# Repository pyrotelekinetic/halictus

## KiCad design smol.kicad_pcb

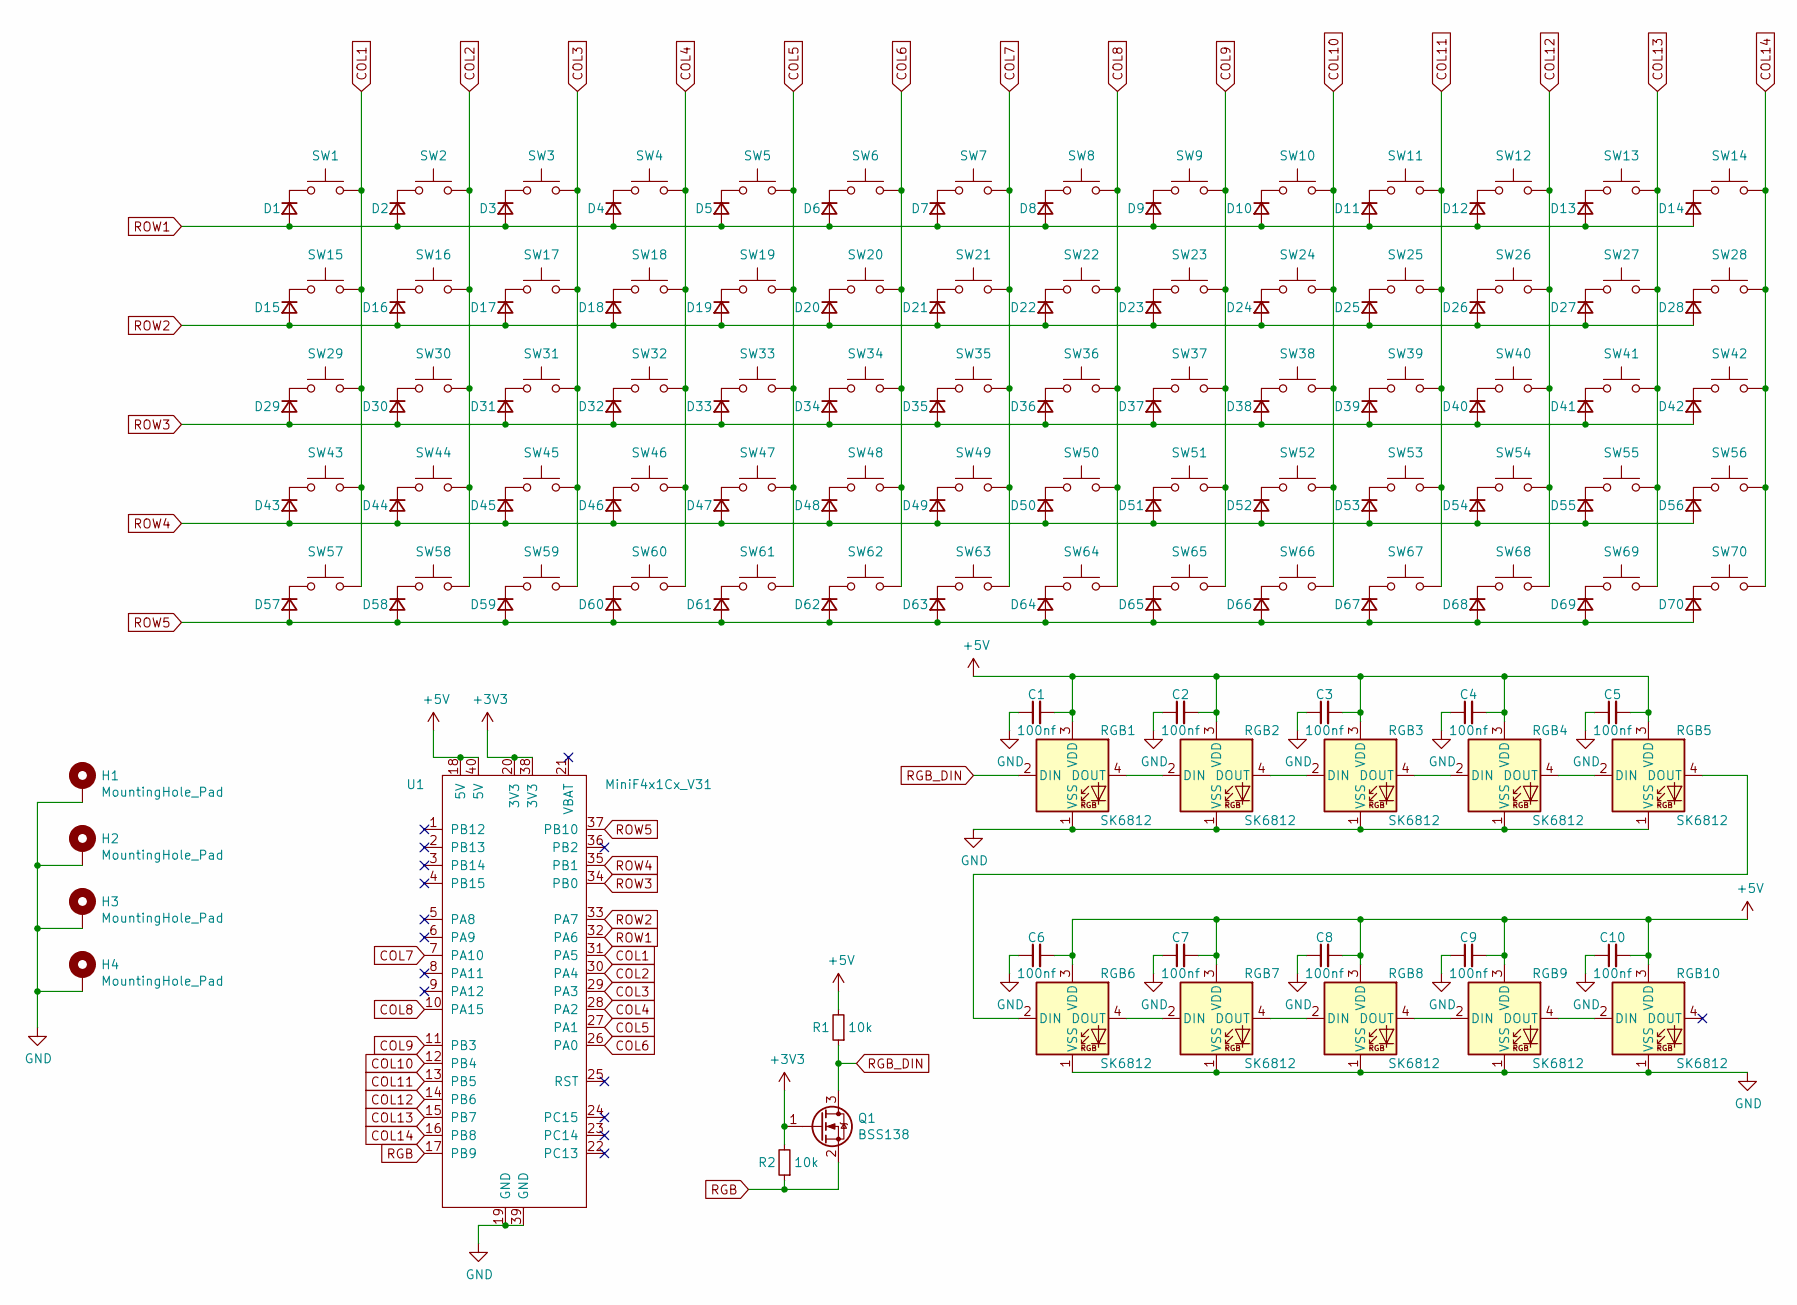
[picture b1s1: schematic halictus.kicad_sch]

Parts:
C1, C2, C3, C4, C5, C6, C7, C8, C9, C10: 100nf; C_0603_1608Metric_Pad1.08x0.95mm_HandSolder
D1, D2, D3, D4, D5, D6, D7, D8, D9, D10, D11, D12, D13, D14, D15, D16, D17, D18, D19, D20, D21, D22, D23, D24, D25, D26, D27, D28, D29, D30, D31, D32, D33, D34, D35, D36, D37, D38, D39, D40, D41, D42, D43, D44, D45, D46, D47, D48, D49, D50, D51, D52, D53, D54, D55, D56, D57, D58, D59, D60, D61, D62, D63, D64, D65, D66, D67, D68, D69, D70: D_Small; D_SOD-123
H1, H2, H3, H4: MountingHole_Pad; MountingHole_2.2mm_M2_Pad_TopBottom
Q1: BSS138; SOT-23
R1, R2: 10k; R_0603_1608Metric_Pad0.98x0.95mm_HandSolder
RGB1, RGB2, RGB3, RGB4, RGB5, RGB6, RGB7, RGB8, RGB9, RGB10: SK6812; LED_SK6812_PLCC4_5.0x5.0mm_P3.2mm
SW1, SW2, SW3, SW4, SW5, SW6, SW7, SW8, SW9, SW10, SW11, SW12, SW13, SW16, SW17, SW18, SW19, SW20, SW21, SW22, SW23, SW24, SW25, SW26, SW27, SW28, SW29, SW30, SW31, SW32, SW33, SW34, SW35, SW36, SW37, SW38, SW39, SW40, SW41, SW44, SW45, SW46, SW47, SW48, SW49, SW50, SW51, SW52, SW53, SW54, SW55, SW56, SW57, SW58, SW59, SW60, SW61, SW62, SW64, SW65, SW66, SW67, SW68, SW69, SW70: 1U; MXOnly-1U-NoLED
SW14, SW15, SW42, SW43: 2U; MXOnly-2U-NoLED
SW63: 2U; MXOnly-2U-ReversedStabilizers-NoLED
U1: MiniF4x1Cx_V31

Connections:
+3V3: Q1.1 (G), R2.2, U1.20 (3V3), U1.38 (3V3)
+5V: C1.2, C2.2, C3.2, C4.2, C5.2, C6.2, C7.2, C8.2, C9.2, C10.2, R1.2, RGB1.3 (VDD), RGB2.3 (VDD), RGB3.3 (VDD), RGB4.3 (VDD), RGB5.3 (VDD), RGB6.3 (VDD), RGB7.3 (VDD), RGB8.3 (VDD), RGB9.3 (VDD), RGB10.3 (VDD), U1.18 (5V), U1.40 (5V)
COL1: SW1.2, SW15.2, SW29.2, SW43.2, SW57.2, U1.31 (PA5)
COL2: SW2.2, SW16.2, SW30.2, SW44.2, SW58.2, U1.30 (PA4)
COL3: SW3.2, SW17.2, SW31.2, SW45.2, SW59.2, U1.29 (PA3)
COL4: SW4.2, SW18.2, SW32.2, SW46.2, SW60.2, U1.28 (PA2)
COL5: SW5.2, SW19.2, SW33.2, SW47.2, SW61.2, U1.27 (PA1)
COL6: SW6.2, SW20.2, SW34.2, SW48.2, SW62.2, U1.26 (PA0)
COL7: SW7.2, SW21.2, SW35.2, SW49.2, SW63.2, U1.7 (PA10)
COL8: SW8.2, SW22.2, SW36.2, SW50.2, SW64.2, U1.10 (PA15)
COL9: SW9.2, SW23.2, SW37.2, SW51.2, SW65.2, U1.11 (PB3)
COL10: SW10.2, SW24.2, SW38.2, SW52.2, SW66.2, U1.12 (PB4)
COL11: SW11.2, SW25.2, SW39.2, SW53.2, SW67.2, U1.13 (PB5)
COL12: SW12.2, SW26.2, SW40.2, SW54.2, SW68.2, U1.14 (PB6)
COL13: SW13.2, SW27.2, SW41.2, SW55.2, SW69.2, U1.15 (PB7)
COL14: SW14.2, SW28.2, SW42.2, SW56.2, SW70.2, U1.16 (PB8)
GND: C1.1, C2.1, C3.1, C4.1, C5.1, C6.1, C7.1, C8.1, C9.1, C10.1, H1.1, H2.1, H3.1, H4.1, RGB1.1 (VSS), RGB2.1 (VSS), RGB3.1 (VSS), RGB4.1 (VSS), RGB5.1 (VSS), RGB6.1 (VSS), RGB7.1 (VSS), RGB8.1 (VSS), RGB9.1 (VSS), RGB10.1 (VSS), U1.19 (GND), U1.39 (GND)
unnamed: D1.1 (K), SW1.1
unnamed: D2.1 (K), SW2.1
unnamed: D3.1 (K), SW3.1
unnamed: D4.1 (K), SW4.1
unnamed: D5.1 (K), SW5.1
unnamed: D6.1 (K), SW6.1
unnamed: D7.1 (K), SW7.1
unnamed: D8.1 (K), SW8.1
unnamed: D9.1 (K), SW9.1
unnamed: D10.1 (K), SW10.1
unnamed: D11.1 (K), SW11.1
unnamed: D12.1 (K), SW12.1
unnamed: D13.1 (K), SW13.1
unnamed: D14.1 (K), SW14.1
unnamed: D15.1 (K), SW15.1
unnamed: D16.1 (K), SW16.1
unnamed: D17.1 (K), SW17.1
unnamed: D18.1 (K), SW18.1
unnamed: D19.1 (K), SW19.1
unnamed: D20.1 (K), SW20.1
unnamed: D21.1 (K), SW21.1
unnamed: D22.1 (K), SW22.1
unnamed: D23.1 (K), SW23.1
unnamed: D24.1 (K), SW24.1
unnamed: D25.1 (K), SW25.1
unnamed: D26.1 (K), SW26.1
unnamed: D27.1 (K), SW27.1
unnamed: D28.1 (K), SW28.1
unnamed: D29.1 (K), SW29.1
unnamed: D30.1 (K), SW30.1
unnamed: D31.1 (K), SW31.1
unnamed: D32.1 (K), SW32.1
unnamed: D33.1 (K), SW33.1
unnamed: D34.1 (K), SW34.1
unnamed: D35.1 (K), SW35.1
unnamed: D36.1 (K), SW36.1
unnamed: D37.1 (K), SW37.1
unnamed: D38.1 (K), SW38.1
unnamed: D39.1 (K), SW39.1
unnamed: D40.1 (K), SW40.1
unnamed: D41.1 (K), SW41.1
unnamed: D42.1 (K), SW42.1
unnamed: D43.1 (K), SW43.1
unnamed: D44.1 (K), SW44.1
unnamed: D45.1 (K), SW45.1
unnamed: D46.1 (K), SW46.1
unnamed: D47.1 (K), SW47.1
unnamed: D48.1 (K), SW48.1
unnamed: D49.1 (K), SW49.1
unnamed: D50.1 (K), SW50.1
unnamed: D51.1 (K), SW51.1
unnamed: D52.1 (K), SW52.1
unnamed: D53.1 (K), SW53.1
unnamed: D54.1 (K), SW54.1
unnamed: D55.1 (K), SW55.1
unnamed: D56.1 (K), SW56.1
unnamed: D57.1 (K), SW57.1
unnamed: D58.1 (K), SW58.1
unnamed: D59.1 (K), SW59.1
unnamed: D60.1 (K), SW60.1
unnamed: D61.1 (K), SW61.1
unnamed: D62.1 (K), SW62.1
unnamed: D63.1 (K), SW63.1
unnamed: D64.1 (K), SW64.1
unnamed: D65.1 (K), SW65.1
unnamed: D66.1 (K), SW66.1
unnamed: D67.1 (K), SW67.1
unnamed: D68.1 (K), SW68.1
unnamed: D69.1 (K), SW69.1
unnamed: D70.1 (K), SW70.1
unnamed: RGB1.4 (DOUT), RGB2.2 (DIN)
unnamed: RGB2.4 (DOUT), RGB3.2 (DIN)
unnamed: RGB3.4 (DOUT), RGB4.2 (DIN)
unnamed: RGB4.4 (DOUT), RGB5.2 (DIN)
unnamed: RGB5.4 (DOUT), RGB6.2 (DIN)
unnamed: RGB6.4 (DOUT), RGB7.2 (DIN)
unnamed: RGB7.4 (DOUT), RGB8.2 (DIN)
unnamed: RGB8.4 (DOUT), RGB9.2 (DIN)
unnamed: RGB9.4 (DOUT), RGB10.2 (DIN)
RGB: Q1.2 (S), R2.1, U1.17 (PB9)
RGB_DIN: Q1.3 (D), R1.1, RGB1.2 (DIN)
ROW1: D1.2 (A), D2.2 (A), D3.2 (A), D4.2 (A), D5.2 (A), D6.2 (A), D7.2 (A), D8.2 (A), D9.2 (A), D10.2 (A), D11.2 (A), D12.2 (A), D13.2 (A), D14.2 (A), U1.32 (PA6)
ROW2: D15.2 (A), D16.2 (A), D17.2 (A), D18.2 (A), D19.2 (A), D20.2 (A), D21.2 (A), D22.2 (A), D23.2 (A), D24.2 (A), D25.2 (A), D26.2 (A), D27.2 (A), D28.2 (A), U1.33 (PA7)
ROW3: D29.2 (A), D30.2 (A), D31.2 (A), D32.2 (A), D33.2 (A), D34.2 (A), D35.2 (A), D36.2 (A), D37.2 (A), D38.2 (A), D39.2 (A), D40.2 (A), D41.2 (A), D42.2 (A), U1.34 (PB0)
ROW4: D43.2 (A), D44.2 (A), D45.2 (A), D46.2 (A), D47.2 (A), D48.2 (A), D49.2 (A), D50.2 (A), D51.2 (A), D52.2 (A), D53.2 (A), D54.2 (A), D55.2 (A), D56.2 (A), U1.35 (PB1)
ROW5: D57.2 (A), D58.2 (A), D59.2 (A), D60.2 (A), D61.2 (A), D62.2 (A), D63.2 (A), D64.2 (A), D65.2 (A), D66.2 (A), D67.2 (A), D68.2 (A), D69.2 (A), D70.2 (A), U1.37 (PB10)

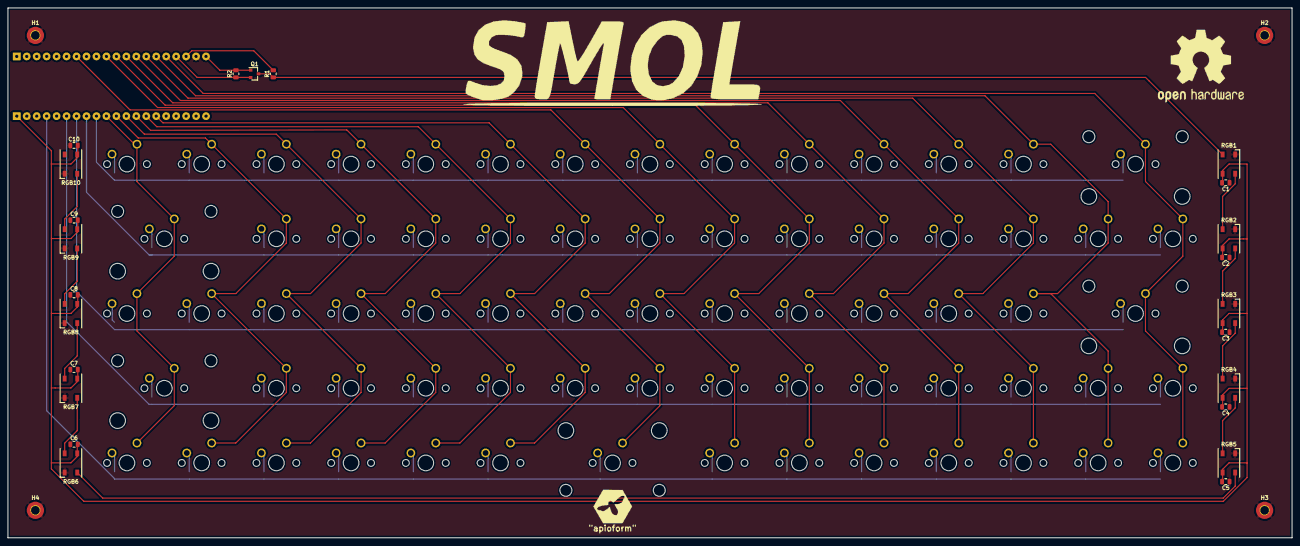
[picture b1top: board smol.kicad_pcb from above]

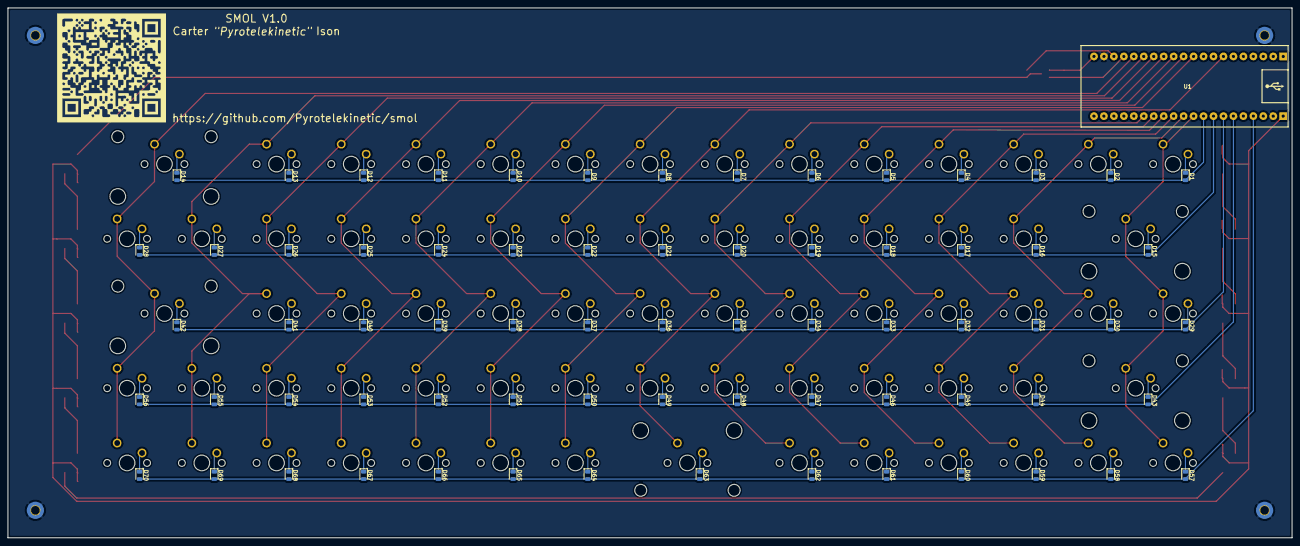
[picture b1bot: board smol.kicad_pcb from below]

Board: 2 copper layers, 327.4 x 135.1 mm, 168 parts (71 on the bottom side), 103 nets.

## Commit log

2021-11-02 init
2021-11-04 add submodules
2021-11-04 add footprint and schematic libraries
2021-11-06 add switch matrix
2021-11-08 add no connects and footprint assignments
2021-11-12 finish matrix schematic
2021-11-12 line up switches in pcb
2021-11-13 move space bar one key to the right
2021-11-13 position diodes on pcb
2021-11-19 switch to mx switch footprints and line up diodes
2021-11-19 connect matrix to blackpill
2021-11-19 add no-connect symbols to unused pins
2021-11-19 use inverted stab on bottow row
2021-11-30 add leds to schematic
2021-12-01 add leds to pcb
2021-12-01 reorganize for easier routing
2021-12-01 flip blackpill to back of pcb
2021-12-18 add ground plane and adjust decoupling caps
2021-12-18 last adjustments before routing
2021-12-18 route matrix rows
2021-12-19 route matrix columns
2021-12-19 route leds
2021-12-20 finish routing
2021-12-28 make all traces same size
2021-12-28 add mounting holes and shift dev board
2021-12-28 finalize and prepare to export for order
2021-12-29 finalize aesthetics
2022-02-07 upgrade to kicad 6.0 and lots of work
2022-02-08 add catgirl silkscreen art
2022-02-08 clean up
